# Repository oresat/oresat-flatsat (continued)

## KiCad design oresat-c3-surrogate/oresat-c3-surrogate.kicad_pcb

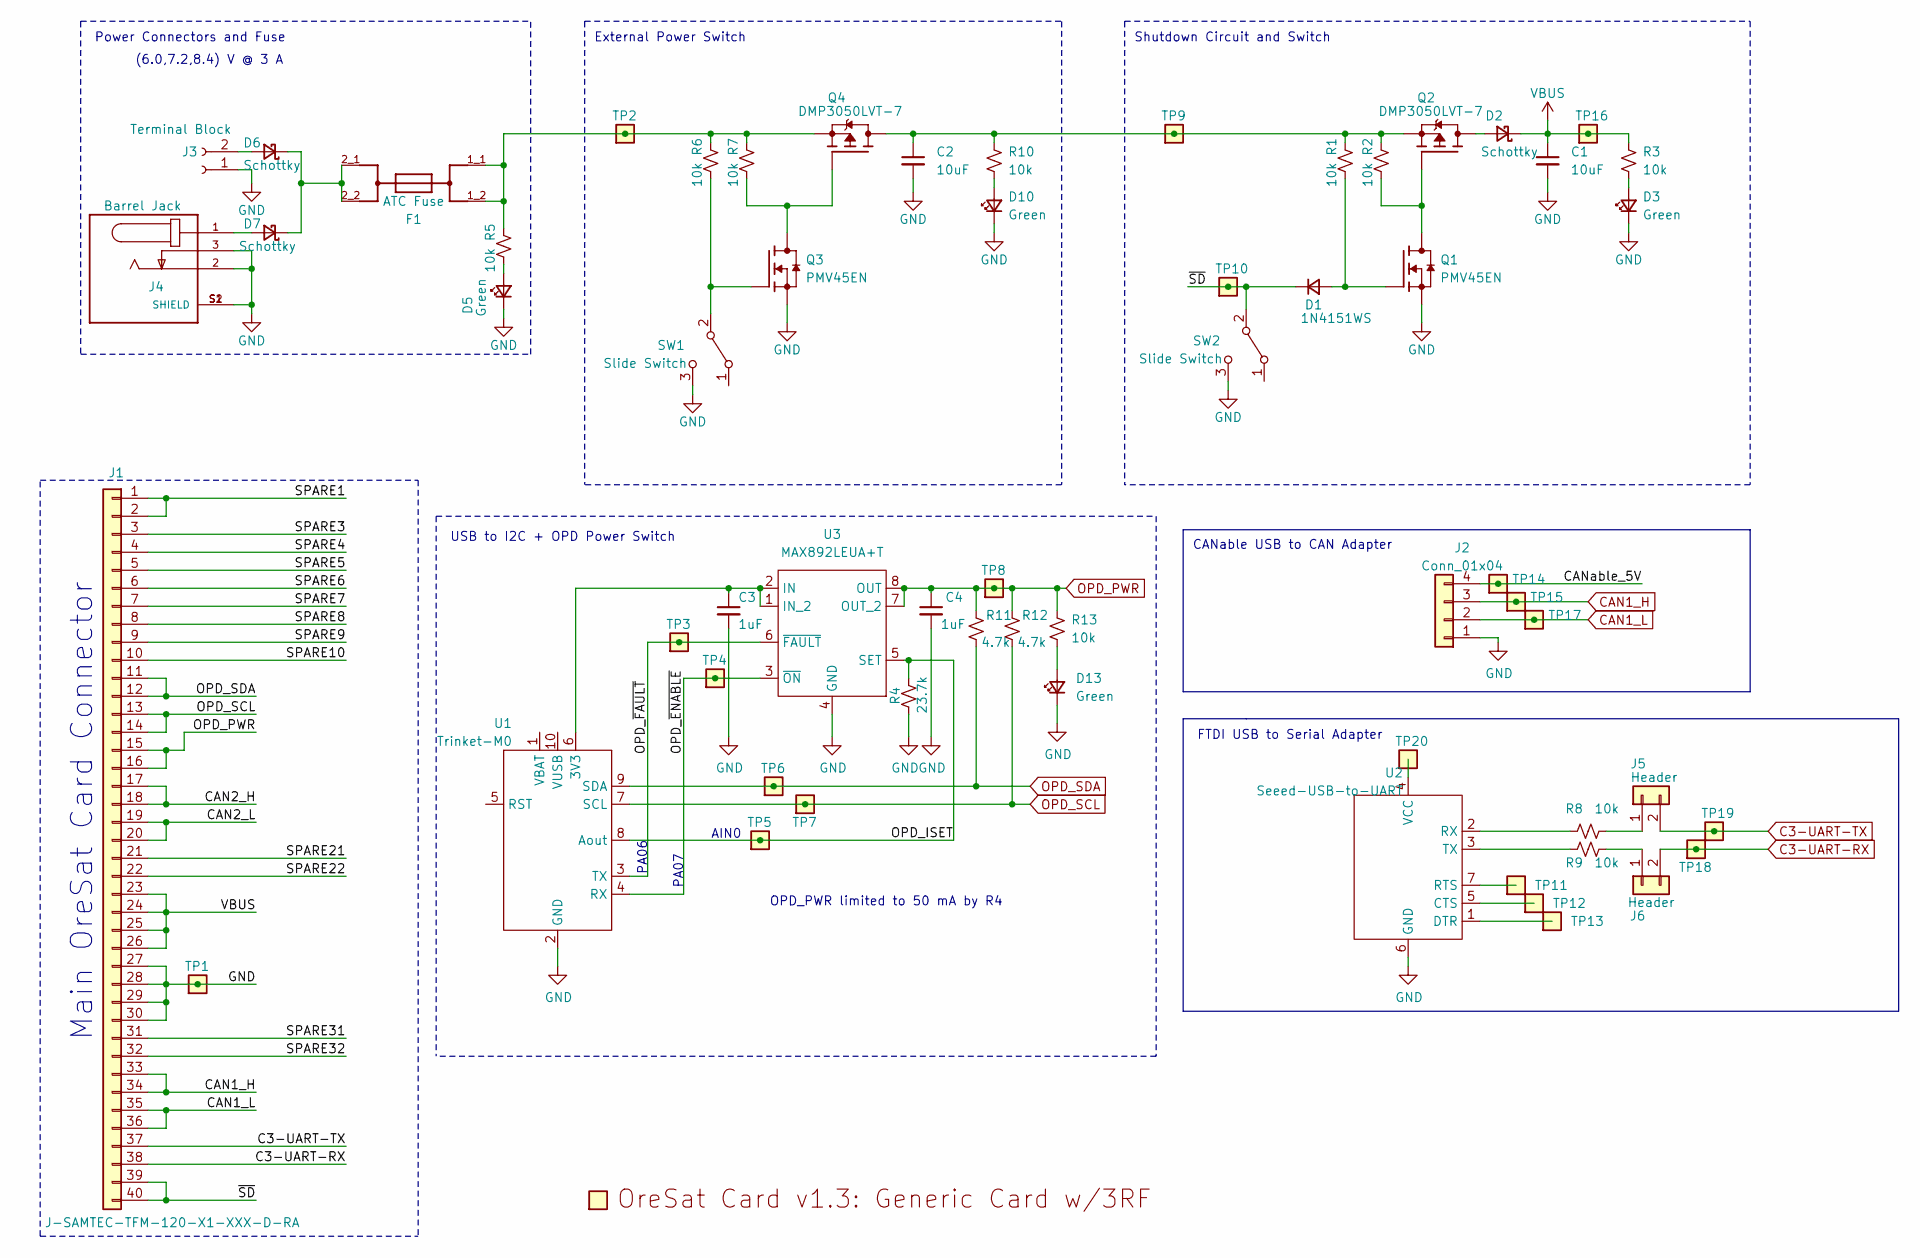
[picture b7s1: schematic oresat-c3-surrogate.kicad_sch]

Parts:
C1, C2: 10uF; C_0603_1608Metric_Pad1.08x0.95mm_HandSolder; MPN GRM188R61A106ME69D
C3, C4: 1uF; C_0603_1608Metric_Pad1.08x0.95mm_HandSolder; MPN GCM188R71E105KA64J
D1: 1N4151WS; D_SOD-323F; MPN 1N4151WS-E3-08
D2, D6, D7: Schottky; D_SMA; MPN SSA33L-E3/61T
D3, D5, D10, D13: Green; LED_0603_1608Metric_Pad1.05x0.95mm_HandSolder; MPN IN-S63AT5G
F1: ATC Fuse; FUSE_3550-2; PARTREV B
J1: J-SAMTEC-TFM-120-X1-XXX-D-RA; MPN TFM-120-01-L-D-RA
J2: Conn_01x04; TerminalBlock_4Ucon_1x04_P3.50mm_Vertical; MPN 0757570441
J3: Terminal Block; 1995499; MPN 1995499
J4: Barrel Jack; CUI_PJ-051AH; PARTREV 1.03
J5, J6: Header; PinHeader_1x02_P2.54mm_Horizontal; MPN PH1RB-02-UA
PCB1: ORESAT-CARD-V1.3-GENERIC-3RF
Q1, Q3: PMV45EN; SOT23-3; MPN PMV45EN2R
Q2, Q4: DMP3050LVT-7; SOT23-6; MPN DMP3050LVT-7
R1, R2, R3, R5, R6, R7, R8, R9, R10, R13: 10k; R_0603_1608Metric_Pad0.98x0.95mm_HandSolder; MPN RNCF0603BTE10K0
R4: 23.7k; R_0603_1608Metric_Pad0.98x0.95mm_HandSolder; MPN RMCF0603FT23K7
R11, R12: 4.7k; R_0603_1608Metric_Pad0.98x0.95mm_HandSolder; MPN RMCF0603FT4K70
SW1, SW2: Slide Switch; AYZ0102AGRLC; MPN AYZ0102AGRLC
TP1, TP2, TP3, TP4, TP5, TP6, TP7, TP8, TP9, TP10, TP11, TP12, TP13, TP14, TP15, TP16, TP17, TP18, TP19, TP20: TEST-POINT-LARGE-SQUARE; 1X01
U1: Trinket-M0; MPN 3500
U2: Seeed-USB-to-UART; MPN 103990049
U3: MAX892LEUA+T; MPN MAX892LEUA+

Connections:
/CAN2_H: J1.17, J1.18
/CAN2_L: J1.19, J1.20
/CANable_5V: J2.4, TP14.1
/OPD_ISET: R4.1, TP5.1, U1.8 (Aout), U3.5 (SET)
/OPD_~ENABLE: TP4.1, U1.4 (RX), U3.3 (~ON)
/OPD_~FAULT: TP3.1, U1.3 (TX), U3.6 (~FAULT)
/SPARE1: J1.1, J1.2
/SPARE3: J1.3
/SPARE4: J1.4
/SPARE5: J1.5
/SPARE6: J1.6
/SPARE7: J1.7
/SPARE8: J1.8
/SPARE9: J1.9
/SPARE10: J1.10
/SPARE21: J1.21
/SPARE22: J1.22
/SPARE31: J1.31
/SPARE32: J1.32
/~SD: D1.1 (K), J1.39, J1.40, SW2.2 (B), TP10.1
C3-UART-RX: J1.38, J6.2, TP18.1
C3-UART-TX: J1.37, J5.2, TP19.1
CAN1_H: J1.33, J1.34, J2.3, TP15.1
CAN1_L: J1.35, J1.36, J2.2, TP17.1
GND: C1.2, C2.2, C3.2, C4.2, D3.1 (K), D5.1 (K), D10.1 (K), D13.1 (K), J1.27, J1.28, J1.29, J1.30, J2.1, J3.1, J4.2, J4.3, J4.S1 (SHIELD), J4.S2 (SHIELD), Q1.2, Q3.2, R4.2, SW1.3 (C), SW2.3 (C), TP1.1, U1.2 (GND), U2.6 (GND), U3.4 (GND)
unnamed: C2.1, Q2.4, Q4.1, Q4.2, Q4.5, Q4.6, R1.1, R2.1, R10.1, TP9.1
unnamed: C3.1, U1.6 (3V3), U3.1 (IN_2), U3.2 (IN)
unnamed: D1.2 (A), Q1.1, R1.2
unnamed: D2.2 (A), Q2.1, Q2.2, Q2.5, Q2.6
unnamed: D3.2 (A), R3.2
unnamed: D5.2 (A), R5.2
unnamed: D6.1 (K), D7.1 (K), F1.2_1, F1.2_2
unnamed: D6.2 (A), J3.2
unnamed: D7.2 (A), J4.1
unnamed: D10.2 (A), R10.2
unnamed: D13.2 (A), R13.2
unnamed: F1.1_1, F1.1_2, Q4.4, R5.1, R6.1, R7.1, TP2.1
unnamed: J5.1, R8.2
unnamed: J6.1, R9.2
unnamed: Q1.3, Q2.3, R2.2
unnamed: Q3.1, R6.2, SW1.2 (B)
unnamed: Q3.3, Q4.3, R7.2
unnamed: R8.1, U2.2 (RX)
unnamed: R9.1, U2.3 (TX)
unnamed: TP11.1, U2.7 (RTS)
unnamed: TP12.1, U2.5 (CTS)
unnamed: TP13.1, U2.1 (DTR)
unnamed: TP20.1, U2.4 (VCC)
OPD_PWR: C4.1, J1.15, J1.16, R11.1, R12.1, R13.1, TP8.1, U3.7 (OUT_2), U3.8 (OUT)
OPD_SCL: J1.13, J1.14, R12.2, TP7.1, U1.7 (SCL)
OPD_SDA: J1.11, J1.12, R11.2, TP6.1, U1.9 (SDA)
VBUS: C1.1, D2.1 (K), J1.23, J1.24, J1.25, J1.26, R3.1, TP16.1

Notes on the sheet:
Power Connectors and Fuse
Main OreSat Card Connector
(6.0,7.2,8.4) V @ 3 A
USB to I2C + OPD Power Switch
External Power Switch
PA06
PA07
AIN0
OPD_PWR limited to 50 mA by R4
Shutdown Circuit and Switch
CANable USB to CAN Adapter
FTDI USB to Serial Adapter

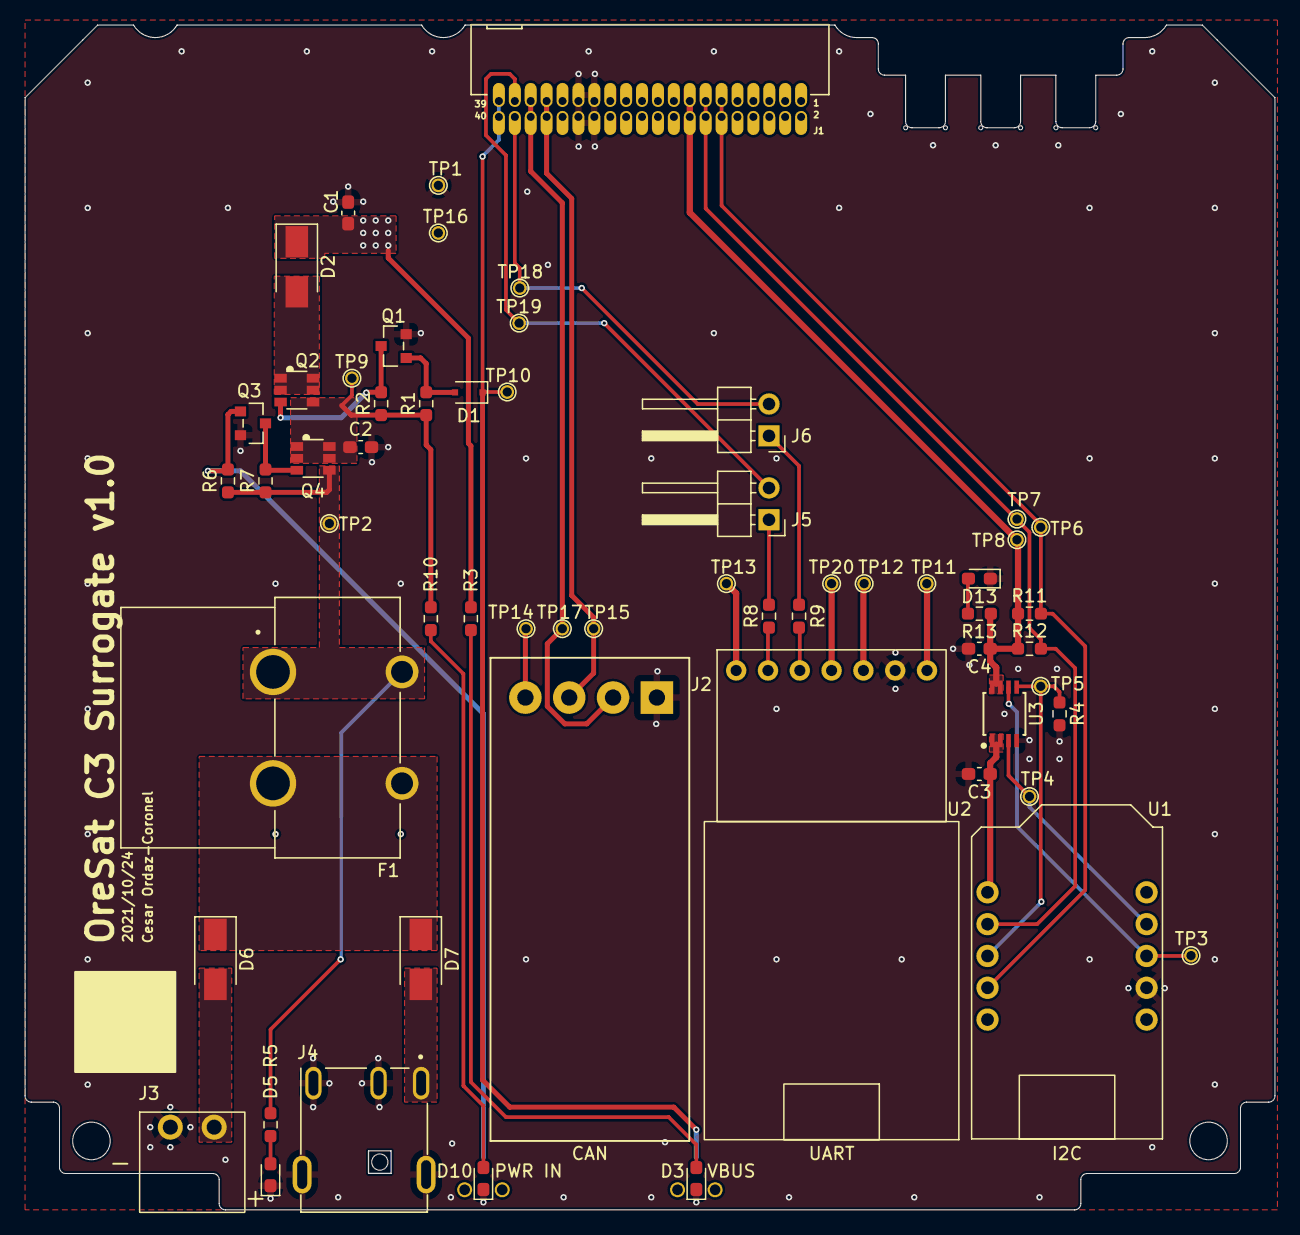
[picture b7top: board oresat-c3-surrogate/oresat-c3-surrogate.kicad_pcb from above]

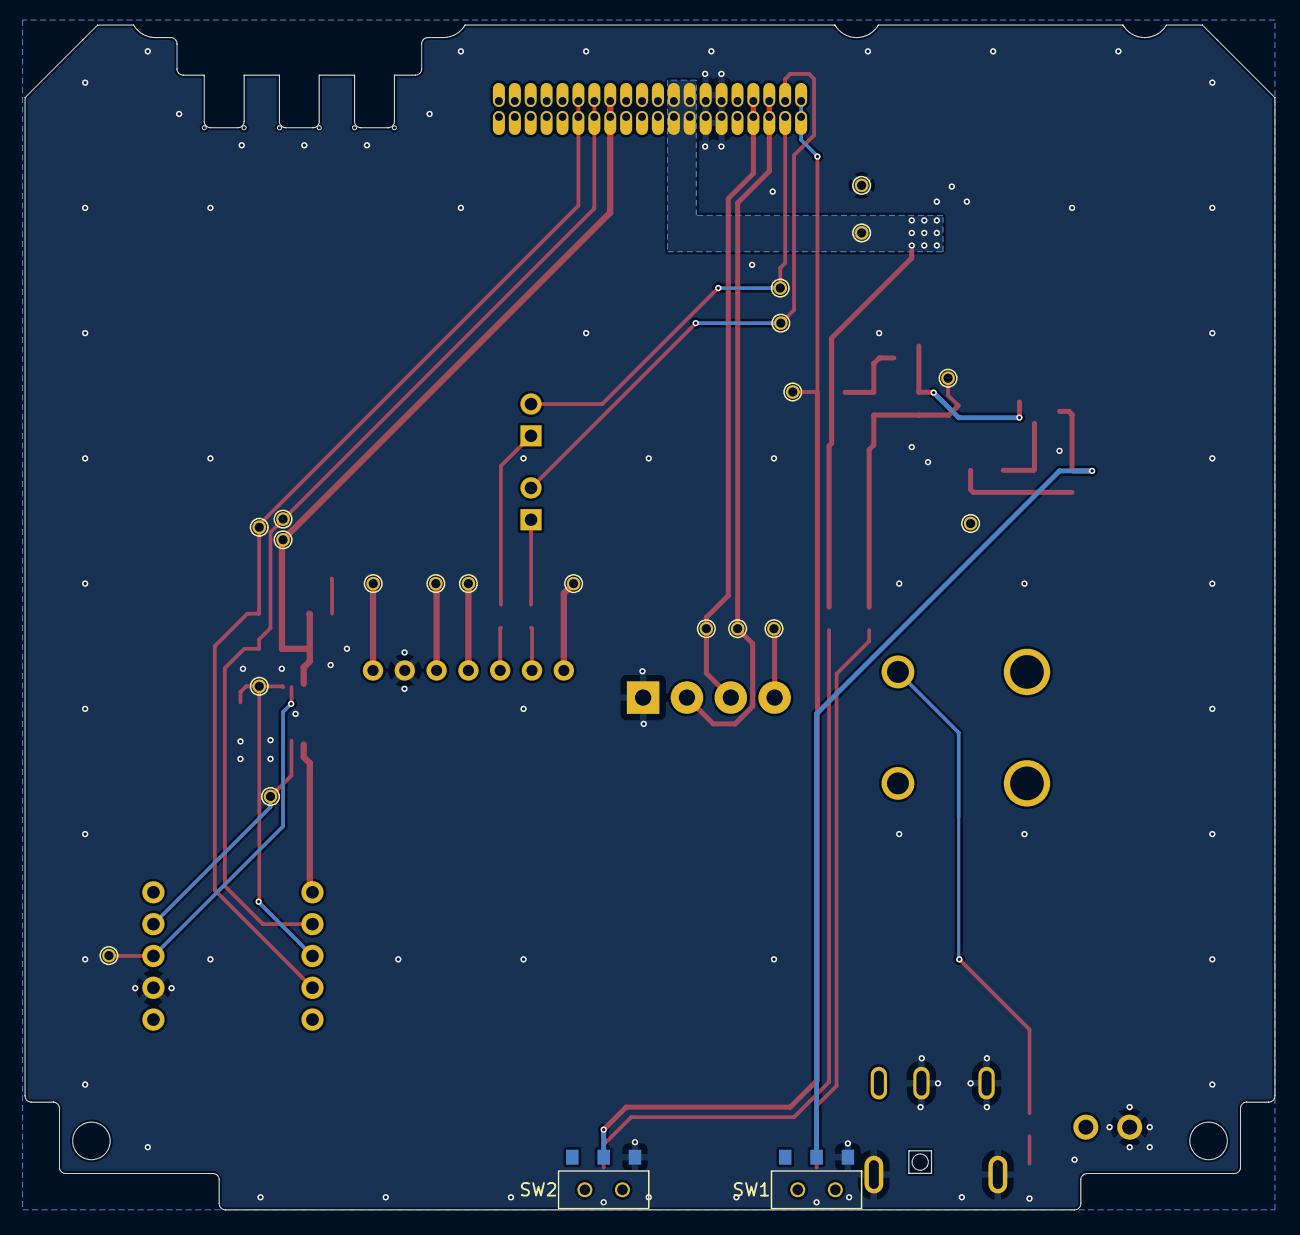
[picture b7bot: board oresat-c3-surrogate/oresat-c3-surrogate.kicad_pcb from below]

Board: 2 copper layers, 99.8 x 94.6 mm, 62 parts (2 on the bottom side), 40 nets.

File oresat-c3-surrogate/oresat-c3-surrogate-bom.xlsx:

OreSat C3 Surrogate Board v1.0 BOM revision 0
Qty | Parts | MFR | MPN | Description | DIST | DPN | P/NP
2 | C1, C2, | Murata | GRM188R61A106ME69D | CAP CER 10UF 10V X5R 0603 | Digi-Key | 490-10475-1-ND | P
2 | C3, C4, | Murata | GCM188R71E105KA64J | CAP CER 1UF 25V X7R 0603 | Digi-Key | 490-GCM188R71E105KA64JCT-ND | P
1 | D1, | Vishay | 1N4151WS-E3-08 | DIODE GEN PURP 50V 150MA SOD323 | Digi-Key | 112-1N4151WS-E3-08CT-ND | P
3 | D2, D6, D7, | Vishay | SSA33L-E3/61T | DIODE SCHOTTKY 30V 3A DO214AC | Digi-Key | SSA33L-E3/61TGICT-ND | P
4 | D3, D5, D10, D13, | Inolux | IN-S63AT5G | LED GREEN CLEAR 0603 SMD | Digi-Key | 1830-1062-1-ND | P
1 | F1, | Keystone | 3550-2 | FUSE BLOCK BLADE 500V 15A PCB | Digi-Key | 36-3550-2-ND | P
1 | J1, | Samtec | TFM-120-01-L-D-RA | CONN HEADER R/A 40POS 1.27MM | Digi-Key | SAM10145-ND | P
1 | J2, | Molex | 0757570441 | CONN HEADER VERT 4POS 3.5MM | Digi-Key | WM12840-ND | P
1 | J3, | Phoenix Contact | 1995499 | TERM BLOCK HDR 2POS 90DEG 3.5MM | Digi-Key | 277-6718-ND | P
1 | J4, | CUI Devices | PJ-051AH | CONN PWR JACK 2X5.5MM SOLDER | Digi-Key | CP-051AH-ND | P
2 | J5, J6, | Adam Tech | PH1RB-02-UA | CONN HEADER R/A 2POS 2.54MM | Digi-Key | 2057-PH1RB-02-UA-ND | P
2 | Q1, Q3, | Nexperia | PMV45EN2R | MOSFET N-CH 30V 4.1A TO236AB | Digi-Key | 1727-2307-1-ND | P
2 | Q2, Q4, | Diodes Incorporated | DMP3050LVT-7 | MOSFET P CH 30V 4.5A TSOT26 | Digi-Key | DMP3050LVT-7DICT-ND | P
10 | R1, R2, R3, R5, R6, R7, R8, R9, R10, R13, | Stackpole | RNCF0603BTE10K0 | RES 10K OHM 0.1% 1/10W 0603 | Digi-Key | RNCF0603BTE10K0CT-ND | P
1 | R4, | Stackpole | RMCF0603FT23K7 | RES 23.7K OHM 1% 1/10W 0603 | Digi-Key | RMCF0603FT23K7CT-ND | P
2 | R11, R12, | Stackpole | RMCF0603FT4K70 | RES 4.7K OHM 1% 1/10W 0603 | Digi-Key | RMCF0603FT4K70CT-ND | P
2 | SW1, SW2, | C&K | AYZ0102AGRLC | SWITCH SLIDE SPDT 100MA 12V | Digi-Key | 401-2012-1-ND | P
1 | U1, | Adafruit | 3500 | TRINKET M0 ATSAMD21E18 EVAL BRD | Digi-Key | 1528-2361-ND | P
1 | U2, | Seeed | 103990049 | USB TO UART 5V/3V3 | Digi-Key | 1597-1332-ND | P
1 | U3, | Maxim | MAX892LEUA+ | IC PWR SWITCH P-CHAN 1:1 8UMAX | Digi-Key | MAX892LEUA+-ND | P
1 |  | CANable |  | CANable
2 |  | Adam Tech | PH1-05-UA | CONN HEADER VERT 5POS 2.54MM | Digi-Key | 2057-PH1-05-UA-ND | P
1 |  | Phoenix Contact | 1900468 | 2 Position Terminal Block Plug, Female Sockets 0.138" (3.50mm) | Digi-Key | 277-9008-ND
1 |  | Littlefuse | 0287003.L | FUSE AUTO 3A 32VDC BLADE | Digi-Key | F11059-ND
1 |  | Sullins | PPPC071LGBN-RC | CONN HDR 7POS 0.1 GOLD PCB R/A | Digi-Key | S5482-ND | P
